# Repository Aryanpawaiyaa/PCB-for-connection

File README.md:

# PCB Collection & Hardware Projects

A centralized repository for hardware designs, electronic modules, and production-ready PCBs.

---

## Projects in this Repository

### 1. [1S × 6 to 6S Series Battery Combiner](./1S_to_6S_Battery_Combiner/)
- **Description:** 4-layer power distribution PCB that connects six individual 1S batteries in series to produce a single 6S output.
- **Inputs:** 6× AMASS XT30-M vertical connectors.
- **Output:** 1× AMASS XT60-F vertical high-current socket.
- **Monitoring:** 1× JST-XH 7-Pin 2.50mm balance port for cell balancing.
- **Current Rating:** 32A continuous (dual parallel 3.5mm power buses), up to 60A burst.
- **Status:** **Production Ready (v1.0)** — Verified with KiCad DRC/ERC; Gerbers generated.

---

### 2. DroneX Battery Carrier (Atopile)
- High-current drone battery distribution module written in Atopile circuits-as-code.

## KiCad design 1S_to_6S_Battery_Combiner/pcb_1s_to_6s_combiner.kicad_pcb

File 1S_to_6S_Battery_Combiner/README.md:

# 1S × 6 to 6S Series Battery Combiner PCB (v1.0)

A production-grade, 4-layer power distribution board designed to connect six individual 1S LiPo/Li-ion batteries in series to produce a single 6S battery output (22.2V nominal / 25.2V max).

## Overview & Specs
- **Inputs:** 6× AMASS XT30 Male vertical through-hole connectors (`J_BAT1` to `J_BAT6`).
- **Output:** 1× AMASS XT60 Female vertical high-current socket (`J_OUT`).
- **Balance Port:** 1× JST-XH 7-Pin 2.50mm vertical balance header (`J_BAL`) for cell monitoring & balance charging.
- **Layers:** 4-Layer FR-4 (1.6mm thickness, 1oz copper outer/inner).
- **Dimensions:** 84 mm × 54 mm with 4× M3 mounting holes.
- **Continuous Current Rating:** 32A continuous ($\Delta T < 10^\circ\text{C}$), up to 60A burst.

## Board Views
| Top View | Bottom View |
| :---: | :---: |
|  |  |

## High-Current Bus Design
- **Parallel Copper Buses:** 3.5mm wide traces on `F.Cu` and `B.Cu` in parallel (equivalent to 7.0mm / 275 mil total copper).
- **Layer Isolation:** Inner layers `In1.Cu` and `In2.Cu` carry shielded balance sense lines with zero planar crossing.
- **Via Stitching:** Array of 14 stitching vias (0.8mm size / 0.4mm drill) along high-current paths.

## Verification
- **KiCad DRC:** 0 Violations, 0 Unconnected Items.
- **KiCad ERC:** 0 Errors.

## Manufacturing & Ordering
The [`pcb_1s_to_6s_combiner_production_gerbers.zip`](pcb_1s_to_6s_combiner_production_gerbers.zip) archive contains standard RS-274X Gerber and Excellon drill files ready for instant ordering on **JLCPCB**, **PCBWay**, or **Seeed Studio**.

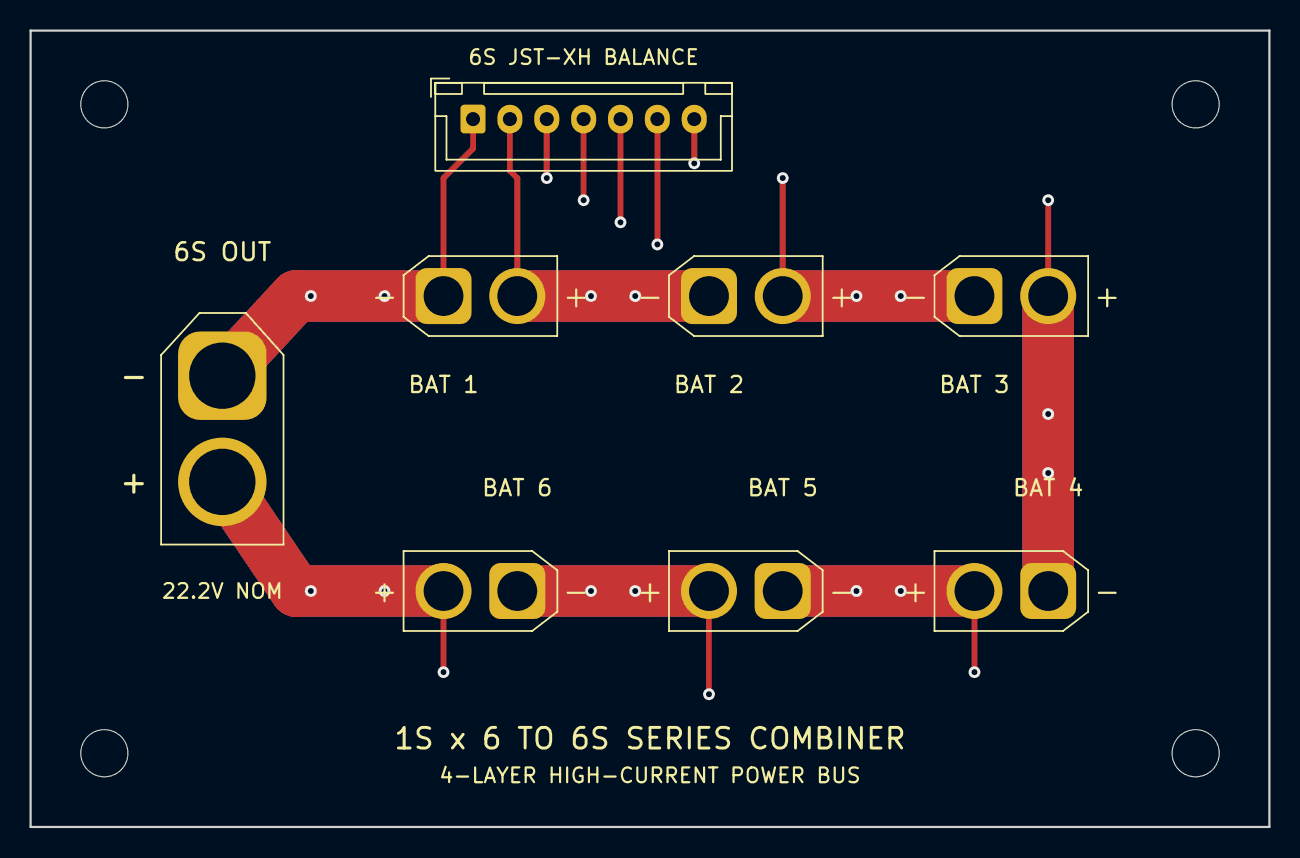
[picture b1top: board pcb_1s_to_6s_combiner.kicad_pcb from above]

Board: 4 copper layers, 84.0 x 54.0 mm, 12 parts (0 on the bottom side), 7 nets.

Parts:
H1, H2, H3, H4: M3_HOLE; MountingHole_3.2mm_M3
J_BAL: JST-XH; JST_XH_B7B-XH-A_1x07_P2.50mm_Vertical
J_BAT1, J_BAT2, J_BAT3, J_BAT4, J_BAT5, J_BAT6: XT30-M; AMASS_XT30U-M_1x02_P5.0mm_Vertical
J_OUT: XT60-F; AMASS_XT60-F_1x02_P7.20mm_Vertical

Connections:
CELL1_POS: J_BAL.2, J_BAT1.2, J_BAT2.1
CELL2_POS: J_BAL.3, J_BAT2.2, J_BAT3.1
CELL3_POS: J_BAL.4, J_BAT3.2, J_BAT4.1
CELL4_POS: J_BAL.5, J_BAT4.2, J_BAT5.1
CELL5_POS: J_BAL.6, J_BAT5.2, J_BAT6.1
GND: J_BAL.1, J_BAT1.1, J_OUT.1
OUT_6S_POS: J_BAL.7, J_BAT6.2, J_OUT.2

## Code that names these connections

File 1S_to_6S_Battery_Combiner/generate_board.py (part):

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    # 1. Setup Nets
    net_names = [
        "GND",          # Net 1: BAT1(-), XT60(-), BAL Pin 1
        "CELL1_POS",    # Net 2: BAT1(+), BAT2(-), BAL Pin 2 (3.7V)
        "CELL2_POS",    # Net 3: BAT2(+), BAT3(-), BAL Pin 3 (7.4V)
        "CELL3_POS",    # Net 4: BAT3(+), BAT4(-), BAL Pin 4 (11.1V)
        "CELL4_POS",    # Net 5: BAT4(+), BAT5(-), BAL Pin 5 (14.8V)
        "CELL5_POS",    # Net 6: BAT5(+), BAT6(-), BAL Pin 6 (18.5V)
        "OUT_6S_POS"    # Net 7: BAT6(+), XT60(+), BAL Pin 7 (22.2V / 25.2V max)
    ]
    nets = {}
    for name in net_names:
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    add_track(nets["GND"], 30.0, 10.0, 28.0, 12.0, 0.4, pcbnew.F_Cu)
    add_track(nets["GND"], 28.0, 12.0, 28.0, 18.0, 0.4, pcbnew.F_Cu)

    # BAL Pin 2 (CELL1_POS) at (32.5, 6.0) -> BAT1 Pad 2 at (33.0, 18.0)
    add_track(nets["CELL1_POS"], 32.5, 6.0, 32.5, 10.0, 0.4, pcbnew.F_Cu)
    add_track(nets["CELL1_POS"], 32.5, 10.0, 33.0, 10.5, 0.4, pcbnew.F_Cu)
    add_track(nets["CELL1_POS"], 33.0, 10.5, 33.0, 18.0, 0.4, pcbnew.F_Cu)

    # BAL Pin 3 (CELL2_POS) at (35.0, 6.0) -> BAT2 Pad 2 at (51.0, 18.0)
    # Routes in upper channel at Y=11.0 on F_Cu (clear of high-current bus at Y=18)
    add_track(nets["CELL2_POS"], 35.0, 6.0, 35.0, 11.0, 0.4, pcbnew.F_Cu)
    add_track(nets["CELL2_POS"], 35.0, 11.0, 51.0, 11.0, 0.4, pcbnew.F_Cu)
    add_track(nets["CELL2_POS"], 51.0, 11.0, 51.0, 18.0, 0.4, pcbnew.F_Cu)

    # BAL Pin 4 (CELL3_POS) at (37.5, 6.0) -> BAT3 Pad 2 at (69.0, 18.0)
    # Routes in upper channel at Y=12.5 on F_Cu
    add_track(nets["CELL3_POS"], 37.5, 6.0, 37.5, 12.5, 0.4, pcbnew.F_Cu)
    add_track(nets["CELL3_POS"], 37.5, 12.5, 69.0, 12.5, 0.4, pcbnew.F_Cu)
    add_track(nets["CELL3_POS"], 69.0, 12.5, 69.0, 18.0, 0.4, pcbnew.F_Cu)

    # BAL Pin 5 (CELL4_POS) at (40.0, 6.0) -> BAT4 Pad 2 at (64.0, 38.0)
    # Routes around right perimeter:
    # From (64.0, 38.0) -> (64.0, 44.0) -> (75.0, 44.0) -> (75.0, 14.0) -> (40.0, 14.0) -> (40.0, 6.0)
    add_track(nets["CELL4_POS"], 64.0, 38.0, 64.0, 44.0, 0.4, pcbnew.F_Cu)
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    add_track(nets["CELL4_POS"], 75.0, 14.0, 40.0, 14.0, 0.4, pcbnew.F_Cu)
    add_track(nets["CELL4_POS"], 40.0, 14.0, 40.0, 6.0, 0.4, pcbnew.F_Cu)

    # BAL Pin 6 (CELL5_POS) at (42.5, 6.0) -> BAT5 Pad 2 at (46.0, 38.0)
    # Routes around right perimeter (concentric outer track):
    # From (46.0, 38.0) -> (46.0, 45.5) -> (76.5, 45.5) -> (76.5, 15.5) -> (42.5, 15.5) -> (42.5, 6.0)
    add_track(nets["CELL5_POS"], 46.0, 38.0, 46.0, 45.5, 0.4, pcbnew.F_Cu)
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    add_track(nets["CELL5_POS"], 76.5, 15.5, 42.5, 15.5, 0.4, pcbnew.F_Cu)
    add_track(nets["CELL5_POS"], 42.5, 15.5, 42.5, 6.0, 0.4, pcbnew.F_Cu)

    # BAL Pin 7 (OUT_6S_POS) at (45.0, 6.0) -> BAT6 Pad 2 at (28.0, 38.0)
    # Routes through the central channel between BAT6 and BAT1:
    # At X=28.0, straight North through central gap to Y=17.0?
    # Wait, BAT1 Pad 1 is at (28.0, 18.0) (GND)!
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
